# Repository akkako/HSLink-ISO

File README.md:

# HS-Link Isolated version hardware repos

This is an HS-Link Isolated version.

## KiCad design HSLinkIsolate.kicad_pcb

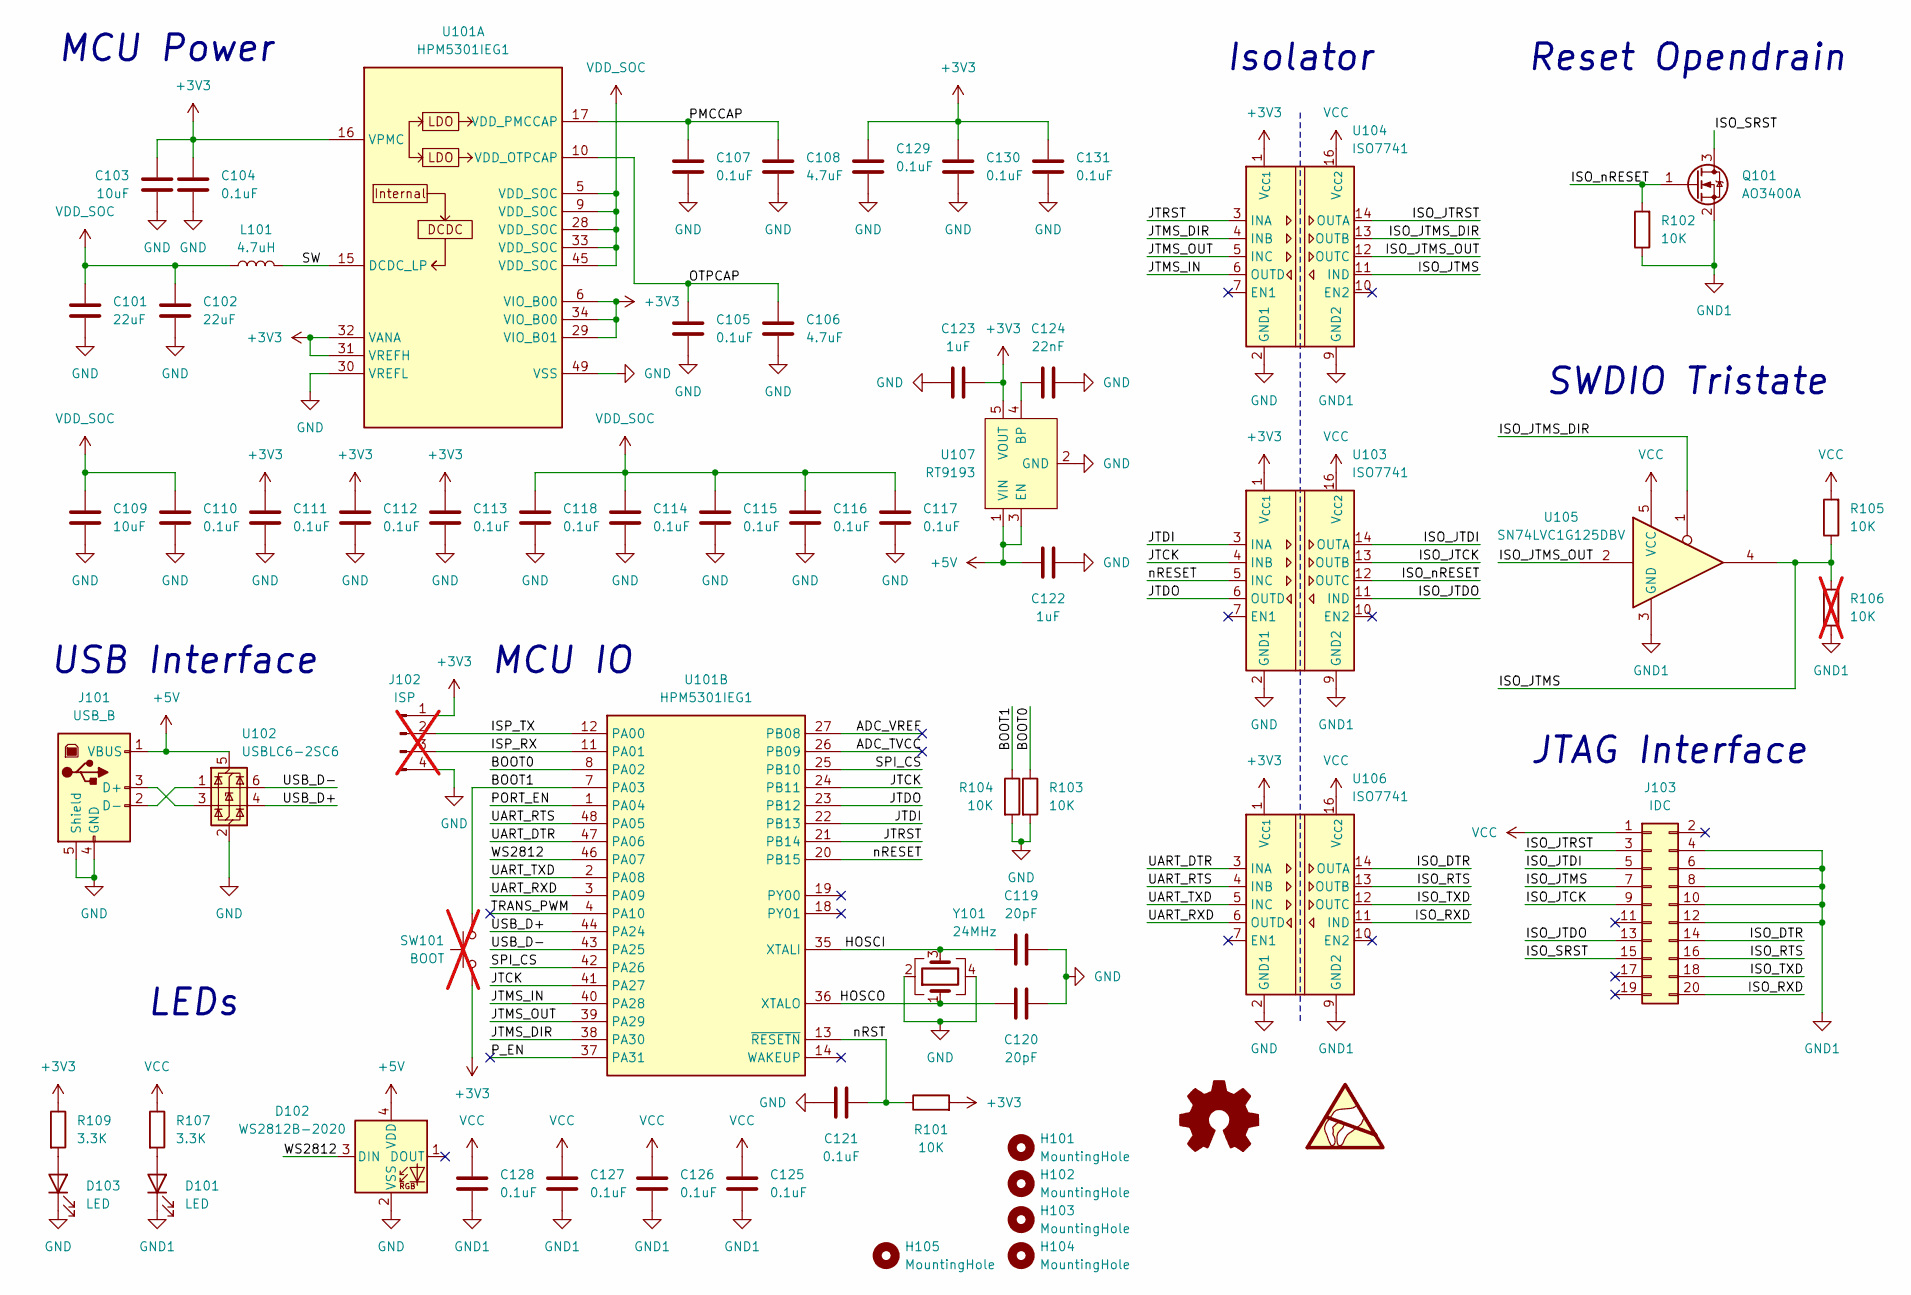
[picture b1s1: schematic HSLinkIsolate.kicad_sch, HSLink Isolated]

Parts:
C101, C102: 22uF; C_0805_2012Metric
C103, C109: 10uF; C_0805_2012Metric
C104, C105, C107, C110, C111, C112, C113, C114, C115, C116, C117, C118, C121, C125, C126, C127, C128, C129, C130, C131: 0.1uF; C_0603_1608Metric
C106, C108: 4.7uF; C_0603_1608Metric
C119, C120: 20pF; C_0603_1608Metric
C122, C123: 1uF; C_0603_1608Metric
C124: 22nF; C_0603_1608Metric
D101, D103: LED; LED_0603_1608Metric
D102: WS2812B-2020; LED_WS2812B-2020_PLCC4_2.0x2.0mm
H101, H102, H103, H104: MountingHole; MountingHole_2.2mm_M2
H105: MountingHole; MountingHole_3.2mm_M3
J101: USB_B; USB_B_Lumberg_2411_02_Horizontal
J102: ISP; PinHeader_1x04_P2.54mm_Vertical; not fitted
J103: IDC; IDC-Header_2x10_P2.54mm_Horizontal
L101: 4.7uH; L_Sunlord_SWPA4020S
Q101: AO3400A; SOT-23
R101, R102, R103, R104, R105: 10K; R_0603_1608Metric
R106: 10K; R_0603_1608Metric; not fitted
R107, R109: 3.3K; R_0603_1608Metric
SW101: BOOT; PinHeader_1x02_P2.54mm_Vertical; not fitted
U101: HPM5301IEG1; QFN-48-1EP_6x6mm_P0.4mm_EP4.2x4.2mm
U102: USBLC6-2SC6; SOT-23-6
U103, U104, U106: ISO7741; QSOP-16_3.9x4.9mm_P0.635mm
U105: SN74LVC1G125DBV; SOT-23-5
U107: RT9193; SOT-23-5
Y101: 24MHz; Crystal_SMD_3225-4Pin_3.2x2.5mm

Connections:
+3V3: C103.1, C104.1, C111.1, C112.1, C113.1, C123.1, C129.1, C130.1, C131.1, J102.1, R101.2, R109.1, SW101.2, U101.6 (VIO_B00), U101.16 (VPMC), U101.29 (VIO_B01), U101.31 (VREFH), U101.32 (VANA), U101.34 (VIO_B00), U103.1 (V_{CC1}), U104.1 (V_{CC1}), U106.1 (V_{CC1}), U107.5 (VOUT)
+5V: C122.1, D102.4 (VDD), J101.1 (VBUS), U102.5 (VBUS), U107.1 (VIN), U107.3 (EN)
/ADC_TVCC: U101.26 (PB09)
/ADC_VREF: U101.27 (PB08)
/BOOT0: R103.1, U101.8 (PA02)
/BOOT1: R104.1, SW101.1, U101.7 (PA03)
/HOSCI: C119.1, U101.35 (XTALI), Y101.3
/HOSCO: C120.1, U101.36 (XTALO), Y101.1
/ISO_DTR: J103.14, U106.14 (OUTA)
/ISO_JTCK: J103.9, U103.13 (OUTB)
/ISO_JTDI: J103.5, U103.14 (OUTA)
/ISO_JTDO: J103.13, U103.11 (IND)
/ISO_JTMS: J103.7, R105.1, R106.2, U104.11 (IND), U105.4
/ISO_JTMS_DIR: U104.13 (OUTB), U105.1
/ISO_JTMS_OUT: U104.12 (OUTC), U105.2
/ISO_JTRST: J103.3, U104.14 (OUTA)
/ISO_RTS: J103.16, U106.13 (OUTB)
/ISO_RXD: J103.20, U106.11 (IND)
/ISO_SRST: J103.15, Q101.3 (D)
/ISO_TXD: J103.18, U106.12 (OUTC)
/ISO_nRESET: Q101.1 (G), R102.2, U103.12 (OUTC)
/ISP_RX: J102.3, U101.11 (PA01)
/ISP_TX: J102.2, U101.12 (PA00)
/JTCK: U101.24 (PB11), U101.41 (PA27), U103.4 (INB)
/JTDI: U101.22 (PB13), U103.3 (INA)
/JTDO: U101.23 (PB12), U103.6 (OUTD)
/JTMS_DIR: U101.38 (PA30), U104.4 (INB)
/JTMS_IN: U101.40 (PA28), U104.6 (OUTD)
/JTMS_OUT: U101.39 (PA29), U104.5 (INC)
/JTRST: U101.21 (PB14), U104.3 (INA)
/OTPCAP: C105.1, C106.1, U101.10 (VDD_OTPCAP)
/PMCCAP: C107.1, C108.1, U101.17 (VDD_PMCCAP)
/PORT_EN: U101.1 (PA04)
/P_EN: U101.37 (PA31)
/SPI_CS: U101.25 (PB10), U101.42 (PA26)
/SW: L101.2, U101.15 (DCDC_LP)
/TRANS_PWM: U101.4 (PA10)
/UART_DTR: U101.47 (PA06), U106.3 (INA)
/UART_RTS: U101.48 (PA05), U106.4 (INB)
/UART_RXD: U101.3 (PA09), U106.6 (OUTD)
/UART_TXD: U101.2 (PA08), U106.5 (INC)
/USB_D+: U101.44 (PA24), U102.4 (I/O2)
/USB_D-: U101.43 (PA25), U102.6 (I/O1)
/WS2812: D102.3 (DIN), U101.46 (PA07)
/nRESET: U101.20 (PB15), U103.5 (INC)
/nRST: C121.1, R101.1, U101.13 (~RESETN)
GND: C101.2, C102.2, C103.2, C104.2, C105.2, C106.2, C107.2, C108.2, C109.2, C110.2, C111.2, C112.2, C113.2, C114.2, C115.2, C116.2, C117.2, C118.2, C119.2, C120.2, C121.2, C122.2, C123.2, C124.2, C129.2, C130.2, C131.2, D102.2 (VSS), D103.1 (K), J101.4 (GND), J101.5 (Shield), J102.4, R103.2, R104.2, U101.30 (VREFL), U101.49 (VSS), U102.2 (GND), U103.2 (GND1), U103.8 (GND1), U104.2 (GND1), U104.8 (GND1), U106.2 (GND1), U106.8 (GND1), U107.2 (GND), Y101.2, Y101.4
GND1: C125.2, C126.2, C127.2, C128.2, D101.1 (K), J103.4, J103.6, J103.8, J103.10, J103.12, Q101.2 (S), R102.1, R106.1, U103.9 (GND2), U103.15 (GND2), U104.9 (GND2), U104.15 (GND2), U105.3 (GND), U106.9 (GND2), U106.15 (GND2)
unnamed: D101.2 (A), R107.2
unnamed: D103.2 (A), R109.2
unnamed: J101.3 (D+), U102.3 (I/O2)
unnamed: J101.2 (D-), U102.1 (I/O1)
unnamed: C124.1, U107.4 (BP)
VCC: C125.1, C126.1, C127.1, C128.1, J103.1, R105.2, R107.1, U103.16 (V_{CC2}), U104.16 (V_{CC2}), U105.5 (VCC), U106.16 (V_{CC2})
VDD_SOC: C101.1, C102.1, C109.1, C110.1, C114.1, C115.1, C116.1, C117.1, C118.1, L101.1, U101.5 (VDD_SOC), U101.9 (VDD_SOC), U101.28 (VDD_SOC), U101.33 (VDD_SOC), U101.45 (VDD_SOC)

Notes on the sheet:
JTAG Interface
Isolator
USB Interface
Reset Opendrain
MCU Power
MCU IO
SWDIO Tristate
LEDs

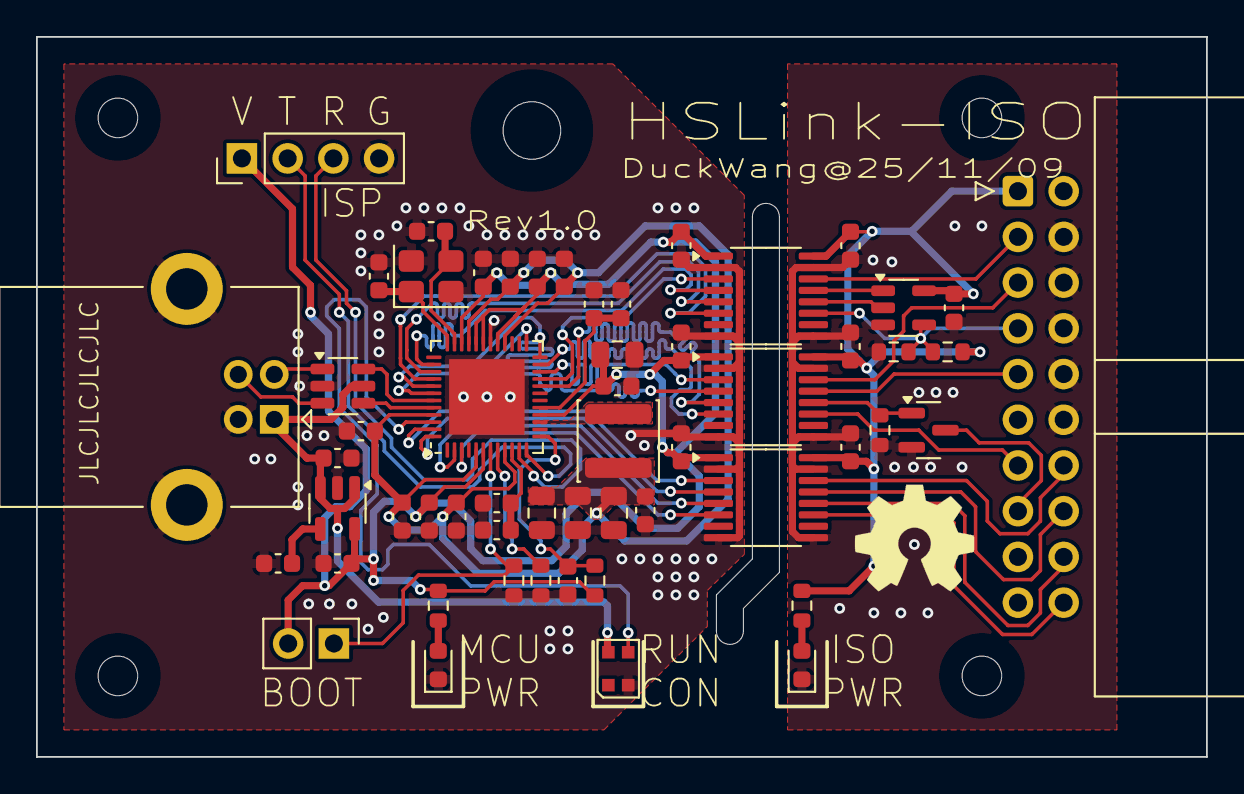
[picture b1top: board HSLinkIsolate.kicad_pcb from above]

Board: 2 copper layers, 65.0 x 40.0 mm, 61 parts (0 on the bottom side), 50 nets.

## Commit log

2025-11-09 add project
2025-11-10 modify pcb
